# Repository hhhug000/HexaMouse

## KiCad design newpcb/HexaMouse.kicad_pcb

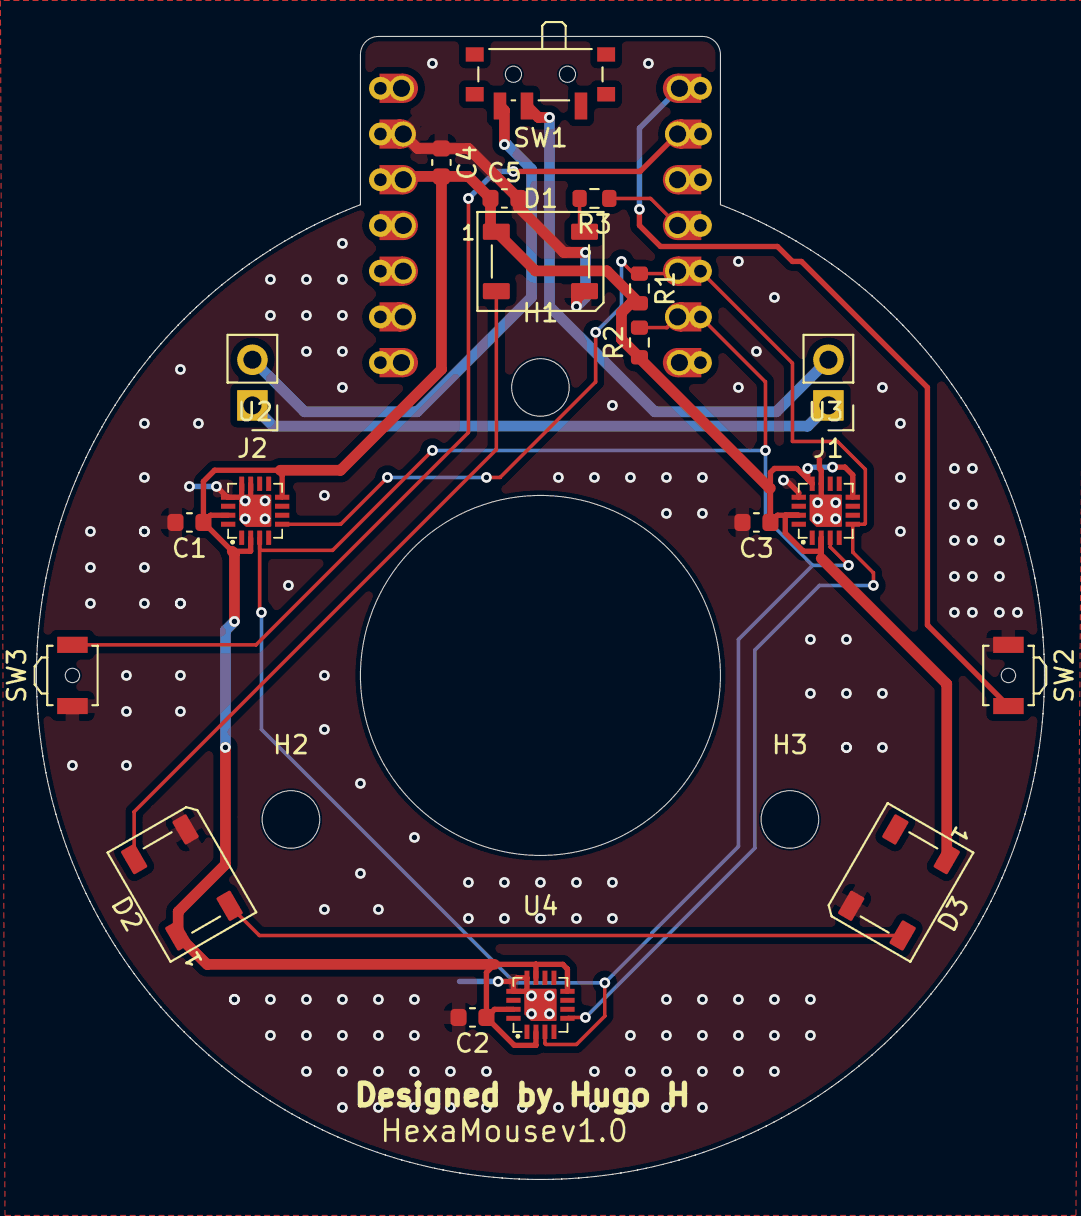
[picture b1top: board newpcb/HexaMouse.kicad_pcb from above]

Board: 2 copper layers, 56.0 x 63.5 mm, 23 parts (1 on the bottom side), 13 nets.

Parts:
C1, C2, C3, C5: 100nF; C_0603_1608Metric
C4: 10uF; C_0603_1608Metric
D1, D2, D3: WS2812B; LED_WS2812B_PLCC4_5.0x5.0mm_P3.2mm
H1, H2, H3: MountingHole; MountingHole_3.2mm_M3
J1, J2: Conn_01x02_Pin; PinHeader_1x02_P2.54mm_Vertical
R1, R2: 10kO; R_0603_1608Metric
R3: 47o; R_0603_1608Metric
SW1: SW_SPDT; SW_SPDT_PCM12
SW2, SW3: SW_Push; SW_SPST_B3U-3000P-B
U1: XIAO-Add-On; XIAO-14P-Add-On
U2, U3, U4: MLX90393SLW-ABA-011-RE; VQFN-16_L3.0-W3.0-P0.50-BL-EP1.7

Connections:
+3.3V: C1.1, C2.1, C3.1, C4.2, C5.1, D1.1 (VDD), D2.1 (VDD), D3.1 (VDD), R1.2, R2.1, U1.12 (3V3_OUT), U2.2 (SENB/CS), U2.8 (VDD_IO), U2.15 (VDD), U3.2 (SENB/CS), U3.8 (VDD_IO), U3.12 (A0), U3.15 (VDD), U4.2 (SENB/CS), U4.8 (VDD_IO), U4.11 (A1), U4.15 (VDD)
GND: C1.2, C2.2, C3.2, C4.1, C5.2, D1.3 (VSS), D2.3 (VSS), D3.3 (VSS), SW2.1, SW3.1, U1.13 (GND), U2.11 (A1), U2.12 (A0), U2.13 (VSS), U2.17 (EP), U3.11 (A1), U3.13 (VSS), U3.17 (EP), U4.12 (A0), U4.13 (VSS), U4.17 (EP)
LED-DATA: R3.1, U1.4 (D3)
unnamed: D1.4 (DIN), R3.2
unnamed: D1.2 (DOUT), D2.4 (DIN)
unnamed: D2.2 (DOUT), D3.4 (DIN)
unnamed: J1.1, J2.1
unnamed: J1.2, SW1.2 (B)
unnamed: J2.2, SW1.3 (C)
SCL: R2.2, U1.6 (D5), U2.3 (SCL/SCLK), U3.3 (SCL/SCLK), U4.3 (SCL/SCLK)
SDA: R1.1, U1.5 (D4), U2.5 (SDA/MOSI), U3.5 (SDA/MOSI), U4.5 (SDA/MOSI)
SW1: SW2.2, U1.1 (D0)
SW2: SW3.2, U1.2 (D1)

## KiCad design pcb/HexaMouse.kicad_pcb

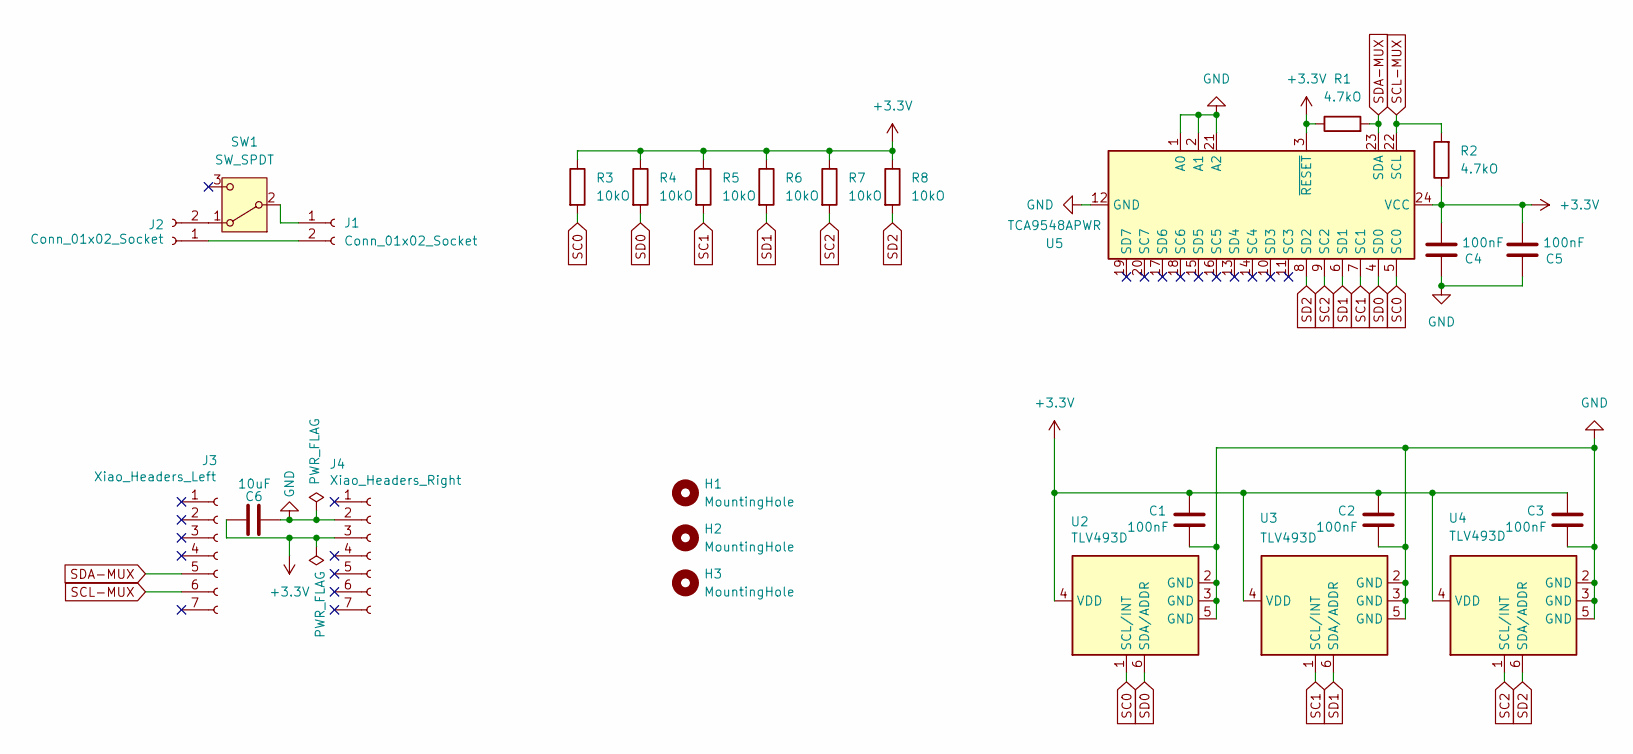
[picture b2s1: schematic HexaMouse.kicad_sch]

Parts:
C1, C2, C3, C4, C5: 100nF; C_0805_2012Metric; LCSC C1711
C6: 10uF; C_0805_2012Metric; LCSC C15850
H1, H2, H3: MountingHole; MountingHole_3.2mm_M3
J1, J2: Conn_01x02_Socket; JST_SH_SM02B-SRSS-TB_1x02-1MP_P1.00mm_Horizontal; LCSC C160402
J3: Xiao_Headers_Left; PinSocket_1x07_P2.54mm_Vertical_SMD_Pin1Left; LCSC C42379199
J4: Xiao_Headers_Right; PinSocket_1x07_P2.54mm_Vertical_SMD_Pin1Right; LCSC C42379199
R1, R2: 4.7kO; R_0805_2012Metric; LCSC C17673
R3, R4, R5, R6, R7, R8: 10kO; R_0805_2012Metric; LCSC C17414
SW1: SW_SPDT; SW_SPDT_PCM12; LCSC C221841
U2, U3, U4: TLV493D; SOT-23-6; LCSC C126688
U5: TCA9548APWR; TSSOP-24_4.4x7.8mm_P0.65mm; LCSC C130026

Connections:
+3.3V: C1.1, C2.1, C3.1, C4.2, C5.2, C6.2, J4.3, R1.1, R2.1, R3.1, R4.1, R5.1, R6.1, R7.1, R8.1, U2.4 (VDD), U3.4 (VDD), U4.4 (VDD), U5.3 (~RESET), U5.24 (VCC)
GND: C1.2, C2.2, C3.2, C4.1, C5.1, C6.1, J4.2, U2.2 (GND), U2.3 (GND), U2.5 (GND), U3.2 (GND), U3.3 (GND), U3.5 (GND), U4.2 (GND), U4.3 (GND), U4.5 (GND), U5.1 (A0), U5.2 (A1), U5.12 (GND), U5.21 (A2)
unnamed: J1.1, SW1.2 (B)
unnamed: J1.2, J2.1
unnamed: J2.2, SW1.1 (A)
SC0: R3.2, U2.1 (SCL/INT), U5.5 (SC0)
SC1: R5.2, U3.1 (SCL/INT), U5.7 (SC1)
SC2: R7.2, U4.1 (SCL/INT), U5.9 (SC2)
SCL-MUX: J3.6, R2.2, U5.22 (SCL)
SD0: R4.2, U2.6 (SDA/ADDR), U5.4 (SD0)
SD1: R6.2, U3.6 (SDA/ADDR), U5.6 (SD1)
SD2: R8.2, U4.6 (SDA/ADDR), U5.8 (SD2)
SDA-MUX: J3.5, R1.2, U5.23 (SDA)

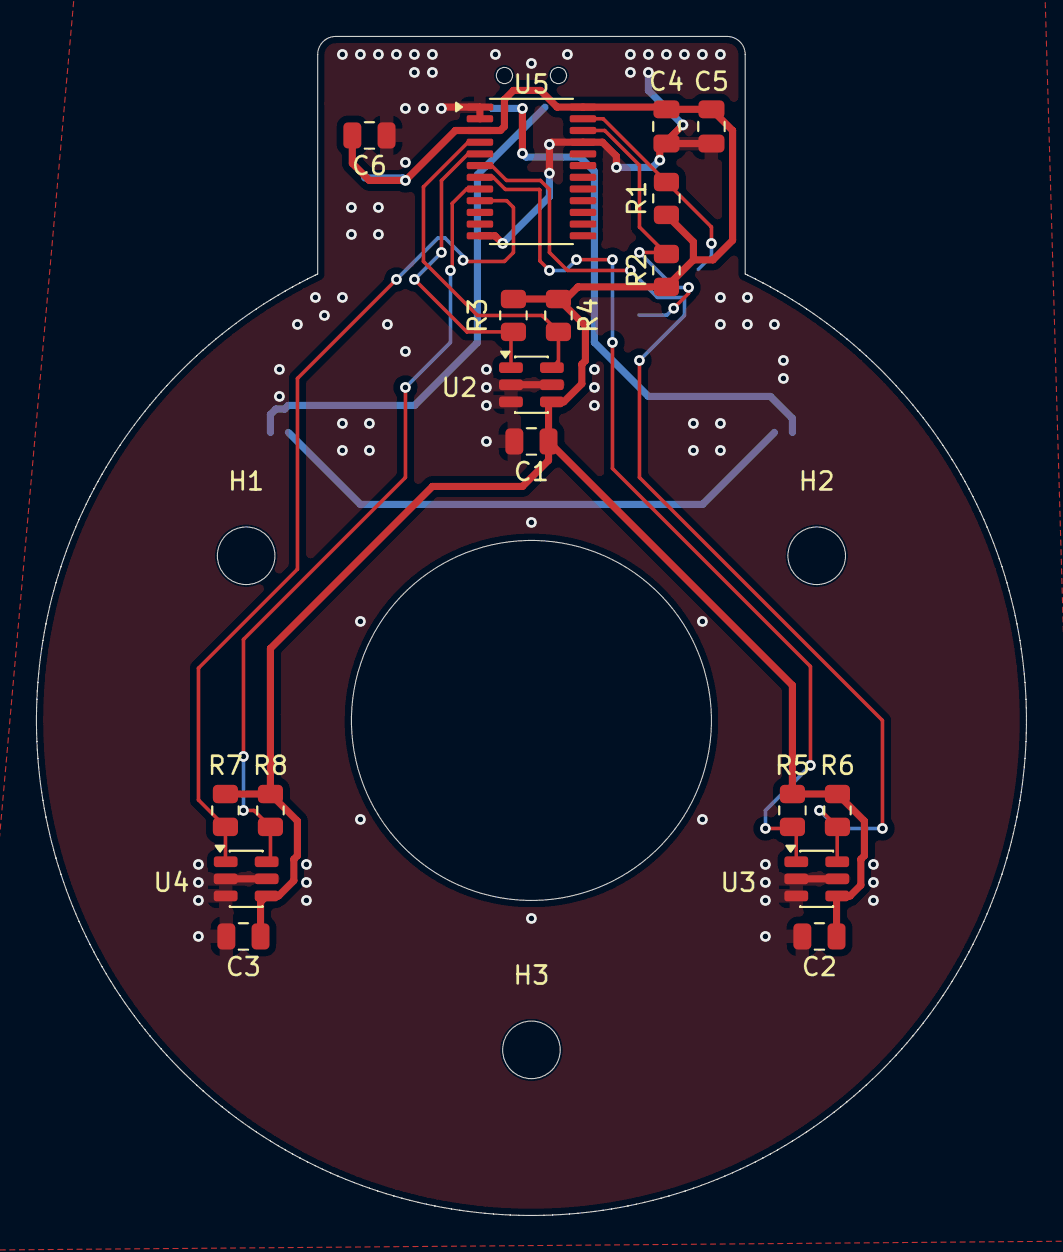
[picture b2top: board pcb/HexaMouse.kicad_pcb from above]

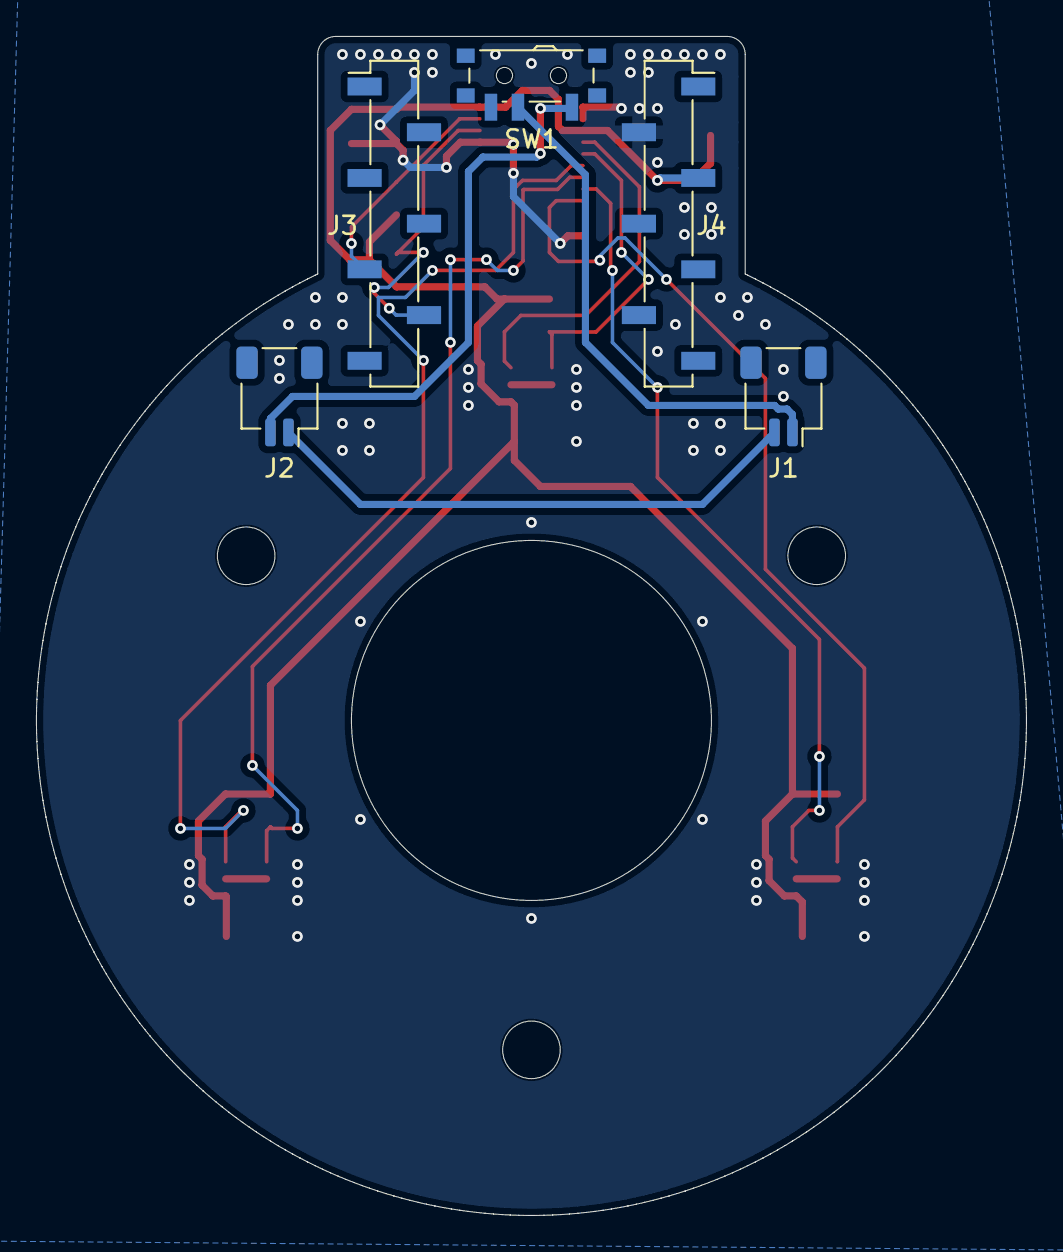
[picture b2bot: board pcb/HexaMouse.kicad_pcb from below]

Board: 2 copper layers, 55.0 x 65.5 mm, 26 parts (5 on the bottom side), 13 nets.
